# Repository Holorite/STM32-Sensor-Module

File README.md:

STM32U031C8T6 sensor module for CottonCandy.

**Debugger Digikey Part #**: 497-STLINK-V3MINIE-ND

Possible Improvements:
1. Use STM32L1 for extended preferred on JLCPCB (alternatives may be possible to reduce assembly cost)
2. Change stlink connector (2x7) to 7 (2x1) 1.27mm pitch headeres so they can be assembled by JLC (2x5 pin interface is also possible)
3. SMD stlink connectors are easier to use (but more expensive)
4. Replace CO2 with a more accurate sensor (SCD40, library very likely available), can remove other sensors too.
5. Change order of CC header pins to match 2.0 interface
6. Add LSE for accurate RTC or LPUART functionality
7. Remove some breakout pins and replace with ready I2C + power for sensor connections
8. Modify interface so module can connect vertically to CottonCandy
9. ADC not usable (with 1/3 bridge) when tested using dry ice (-80C?)

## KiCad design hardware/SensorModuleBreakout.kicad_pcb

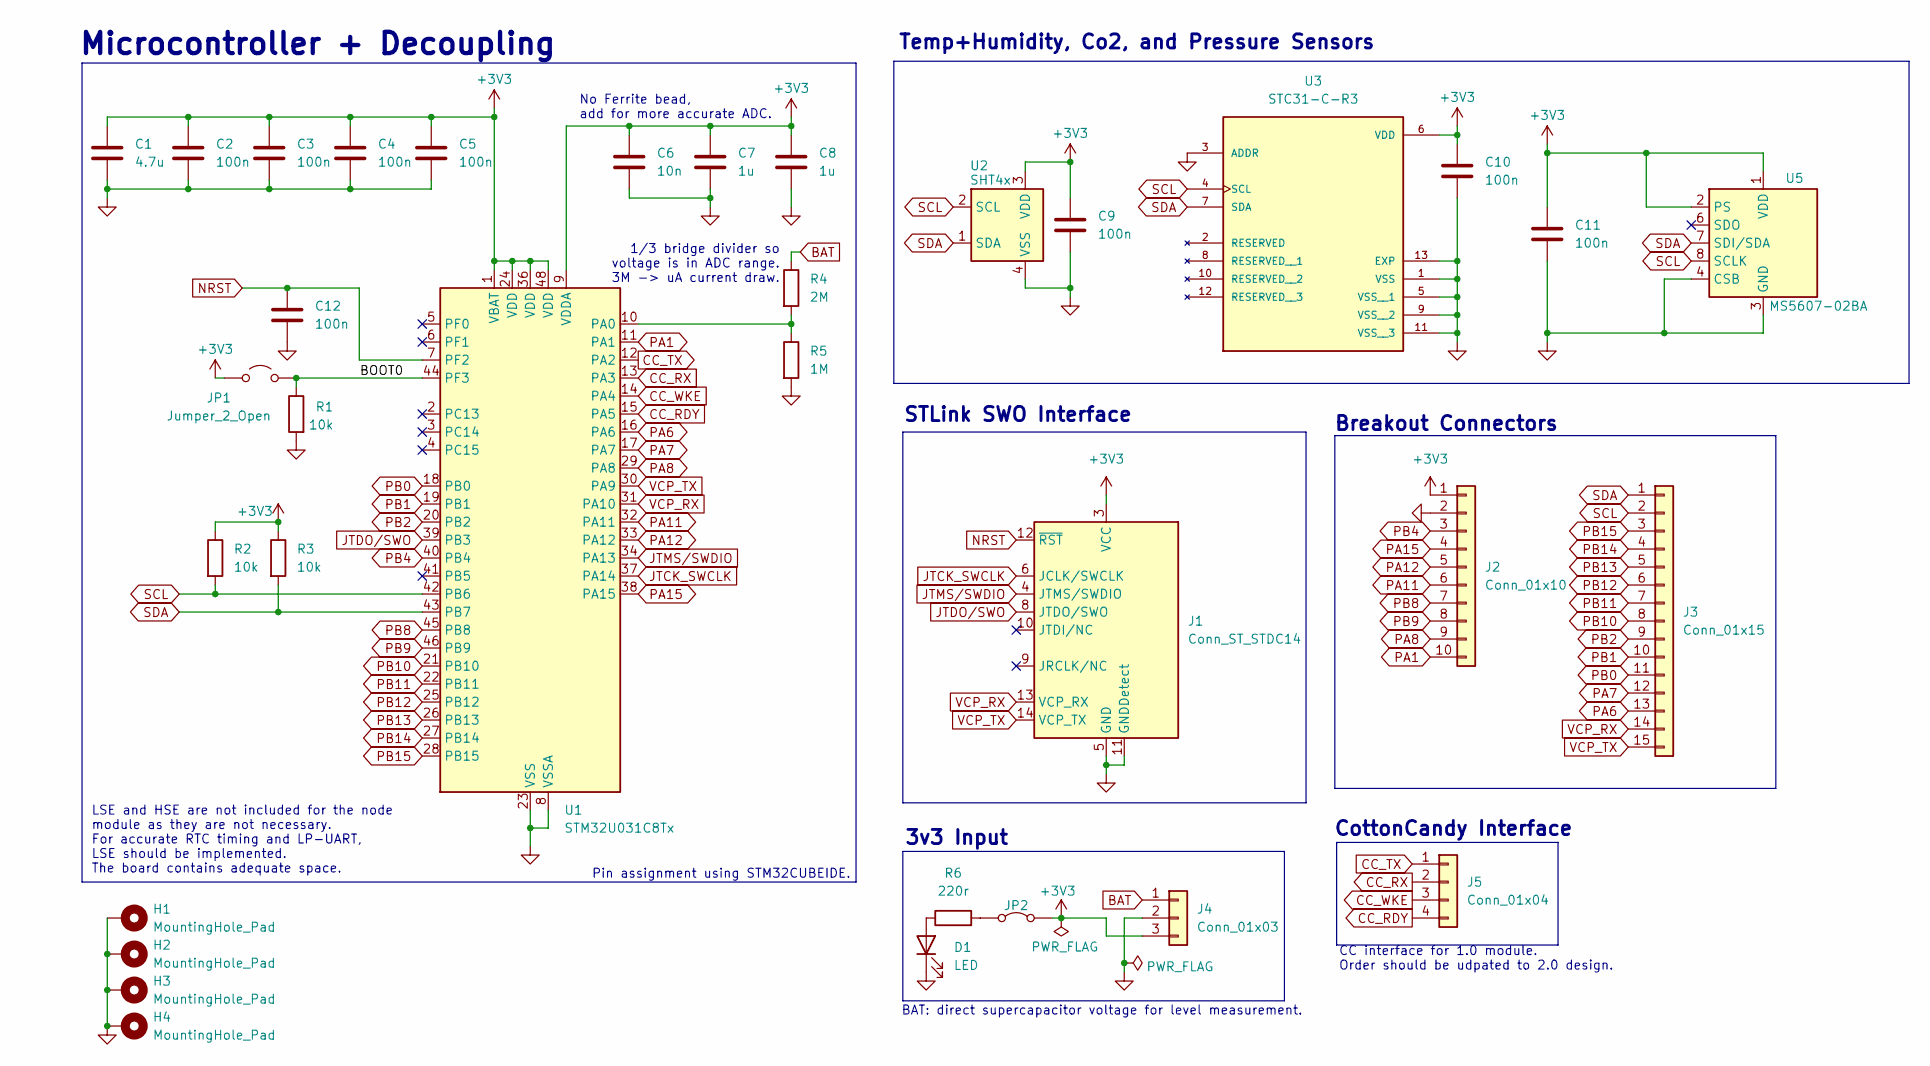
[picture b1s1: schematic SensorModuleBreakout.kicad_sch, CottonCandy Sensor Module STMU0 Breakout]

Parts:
C1: 4.7u; C_0603_1608Metric
C2, C3, C4, C5, C9, C10, C11, C12: 100n; C_0402_1005Metric
C6: 10n; C_0402_1005Metric
C7, C8: 1u; C_0402_1005Metric
D1: LED; LED_0603_1608Metric
H1, H2, H3, H4: MountingHole_Pad; MountingHole_3.2mm_M3_DIN965_Pad
J1: Conn_ST_STDC14; PinHeader_2x07_P1.27mm_Vertical
J2: Conn_01x10; PinHeader_1x10_P2.54mm_Vertical
J3: Conn_01x15; PinHeader_1x15_P2.54mm_Vertical
J4: Conn_01x03; JST_XH_B3B-XH-A_1x03_P2.50mm_Vertical
J5: Conn_01x04; JST_XH_B4B-XH-A_1x04_P2.50mm_Vertical
JP1: Jumper_2_Open; TestPoint_2Pads_Pitch2.54mm_Drill0.8mm
JP2: JP; TestPoint_2Pads_Pitch2.54mm_Drill0.8mm
R1, R2, R3: 10k; R_0402_1005Metric
R4: 2M; R_0603_1608Metric
R5: 1M; R_0402_1005Metric
R6: 220r; R_0402_1005Metric
U1: STM32U031C8Tx; LQFP-48_7x7mm_P0.5mm
U2: SHT4x; Sensirion_DFN-4_1.5x1.5mm_P0.8mm_SHT4x_NoCentralPad
U3: STC31-C-R3; XDCR_STC31-C-R3; PARTREV 3.2
U5: MS5607-02BA; LGA-8_3x5mm_P1.25mm

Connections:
+3V3: C1.1, C2.1, C3.1, C4.1, C5.1, C6.1, C7.1, C8.1, C9.1, C10.1, C11.1, J1.3 (VCC), J2.1, J4.3, JP1.1 (A), JP2.2 (B), R2.1, R3.1, U1.1 (VBAT), U1.9 (VDDA), U1.24 (VDD), U1.36 (VDD), U1.48 (VDD), U2.3 (VDD), U3.6 (VDD), U5.1 (VDD), U5.2 (PS); also elsewhere on the board
/BOOT0: JP1.2 (B), R1.1, U1.44 (PF3)
CC_RDY: J5.4, U1.15 (PA5)
CC_RX: J5.2, U1.13 (PA3)
CC_TX: J5.1, U1.12 (PA2)
CC_WKE: J5.3, U1.14 (PA4)
GND: C1.2, C2.2, C3.2, C4.2, C5.2, C6.2, C7.2, C8.2, C9.2, C10.2, C11.2, C12.2, D1.1 (K), H1.1, H2.1, H3.1, H4.1, J1.5 (GND), J1.7 (GND), J1.11 (GNDDetect), J2.2, J4.2, R1.2, R5.2, U1.8 (VSSA), U1.23 (VSS), U1.35 (VSS), U1.47 (VSS), U2.4 (VSS), U3.1 (VSS), U3.3 (ADDR), U3.5 (VSS__1), U3.9 (VSS__2), U3.11 (VSS__3), U3.13 (EXP), U5.3 (GND), U5.4 (CSB), U5.5 (CSB); also elsewhere on the board
JTCK_SWCLK: J1.6 (JCLK/SWCLK), U1.37 (PA14); also elsewhere on the board
JTDO/SWO: J1.8 (JTDO/SWO), U1.39 (PB3); also elsewhere on the board
JTMS/SWDIO: J1.4 (JTMS/SWDIO), U1.34 (PA13); also elsewhere on the board
NRST: C12.1, J1.12 (~RST), U1.7 (PF2); also elsewhere on the board
unnamed: D1.2 (A), R6.1
unnamed: JP2.1 (A), R6.2
unnamed: R4.2, R5.1, U1.10 (PA0)
PA1: J2.10, U1.11 (PA1)
PA6: J3.13, U1.16 (PA6)
PA7: J3.12, U1.17 (PA7)
PA8: J2.9, U1.29 (PA8)
PA11: J2.6, U1.32 (PA11)
PA12: J2.5, U1.33 (PA12)
PA15: J2.4, U1.38 (PA15)
PB0: J3.11, U1.18 (PB0)
PB1: J3.10, U1.19 (PB1)
PB2: J3.9, U1.20 (PB2)
PB4: J2.3, U1.40 (PB4)
PB8: J2.7, U1.45 (PB8)
PB9: J2.8, U1.46 (PB9)
PB10: J3.8, U1.21 (PB10)
PB11: J3.7, U1.22 (PB11)
PB12: J3.6, U1.25 (PB12)
PB13: J3.5, U1.26 (PB13)
PB14: J3.4, U1.27 (PB14)
PB15: J3.3, U1.28 (PB15)
SCL: J3.2, R2.2, U1.42 (PB6), U2.2 (SCL), U3.4 (SCL), U5.8 (SCLK)
SDA: J3.1, R3.2, U1.43 (PB7), U2.1 (SDA), U3.7 (SDA), U5.7 (SDI/SDA)
VBAT: J4.1, R4.1
VCP_RX: J1.13 (VCP_RX), J3.14, U1.31 (PA10); also elsewhere on the board
VCP_TX: J1.14 (VCP_TX), J3.15, U1.30 (PA9); also elsewhere on the board

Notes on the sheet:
No Ferrite bead, add for more accurate ADC.
Breakout Connectors
Pin assignment using STM32CUBEIDE.
LSE and HSE are not included for the node module as they are not necessary. For accurate RTC timing and LP-UART, LSE should be implemented. The board contains adequate space.
1/3 bridge divider so voltage is in ADC range. 3M -> uA current draw.
3v3 Input
CottonCandy Interface
STLink SWO Interface
Microcontroller + Decoupling
CC interface for 1.0 module. Order should be udpated to 2.0 design.
BAT: direct supercapacitor voltage for level measurement.
Temp+Humidity, Co2, and Pressure Sensors

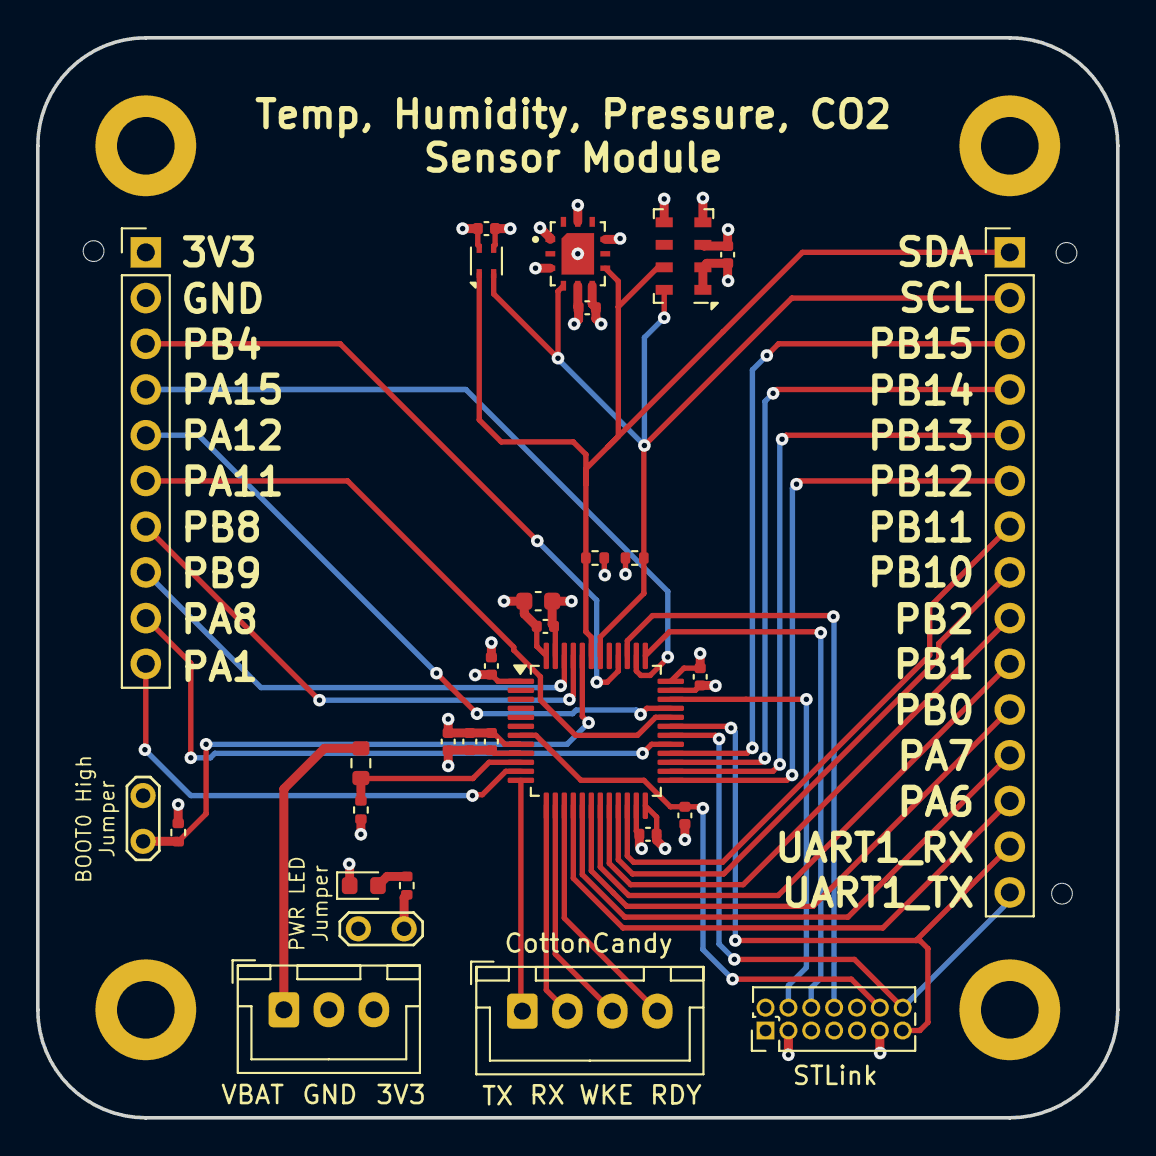
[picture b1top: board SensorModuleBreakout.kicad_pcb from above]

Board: 4 copper layers, 60.0 x 60.0 mm, 34 parts (0 on the bottom side), 38 nets.

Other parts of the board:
STLink: Conn_ST_STDC14; PinHeader_2x07_P1.27mm_Vertical

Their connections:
+3V3: STLink.3 (VCC); also elsewhere on the board
GND: STLink.5 (GND), STLink.7 (GND), STLink.11 (GNDDetect); also elsewhere on the board
JTCK_SWCLK: STLink.6 (JCLK/SWCLK); also elsewhere on the board
JTDO/SWO: STLink.8 (JTDO/SWO); also elsewhere on the board
JTMS/SWDIO: STLink.4 (JTMS/SWDIO); also elsewhere on the board
NRST: STLink.12 (~RST); also elsewhere on the board
VCP_RX: STLink.13 (VCP_RX); also elsewhere on the board
VCP_TX: STLink.14 (VCP_TX); also elsewhere on the board

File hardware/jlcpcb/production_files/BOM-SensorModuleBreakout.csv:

Comment,Designator,Footprint,LCSC,Quantity
10n,C6,C_0402_1005Metric,C15195,1
100n,"C10,C11,C12,C2,C3,C4,C5,C9",C_0402_1005Metric,C1525,8
4.7u,C1,C_0603_1608Metric,C19666,1
STC31-C-R3,U3,XDCR_STC31-C-R3,C22396918,1
LED,D1,LED_0603_1608Metric,C2286,1
2M,R4,R_0603_1608Metric,C22976,1
STM32U031C8Tx,U1,LQFP-48_7x7mm_P0.5mm,C23172783,1
220r,R6,R_0402_1005Metric,C25091,1
10k,"R1,R2,R3",R_0402_1005Metric,C25744,3
1M,R5,R_0402_1005Metric,C26083,1
1u,"C7,C8",C_0402_1005Metric,C52923,2
SHT4x,U2,Sensirion_DFN-4_1.5x1.5mm_P0.8mm_SHT4x_NoCentralPad,C7461861,1
MS5607-02BA,U5,LGA-8_3x5mm_P1.25mm,C97627,1

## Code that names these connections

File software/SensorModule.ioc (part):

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Mcu.Name=STM32U031C8Tx
Mcu.Package=LQFP48
Mcu.UserName=STM32U031C8Tx
PA0.Mode=IN4
PA0.Signal=ADC1_IN4
PA10.Mode=Asynchronous
PA10.Signal=USART1_RX
PA13\ (SWDIO).Mode=Trace_Asynchronous_SW
PA13\ (SWDIO).Signal=DEBUG_JTMS-SWDIO
PA14\ (SWCLK).Mode=Trace_Asynchronous_SW
PA14\ (SWCLK).Signal=DEBUG_JTCK-SWCLK
PA2.Mode=Asynchronous
PA2.Signal=USART2_TX
PA3.Mode=Asynchronous
PA3.Signal=USART2_RX
PA4.GPIOParameters=GPIO_PuPd,GPIO_Label
PA4.GPIO_Label=WKE
PA4.GPIO_PuPd=GPIO_PULLDOWN
PA4.Signal=GPXTI4
PA5.GPIOParameters=GPIO_PuPd,GPIO_Label
PA5.GPIO_Label=RDY
PA5.GPIO_PuPd=GPIO_PULLDOWN
PA5.Signal=GPXTI5
PA9.Mode=Asynchronous
PA9.Signal=USART1_TX
PB3.Mode=Trace_Asynchronous_SW
PB3.Signal=DEBUG_JTDO-SWO
PB6.Mode=I2C
PB6.Signal=I2C1_SCL
PB7.Mode=I2C
PB7.Signal=I2C1_SDA
RCC.HSE_VALUE=4000000
RCC.SYSCLKFreq_VALUE=16000000
board=custom

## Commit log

2025-04-01 gitignore
2025-04-01 add files
2025-04-01 add comment on MCU choice
